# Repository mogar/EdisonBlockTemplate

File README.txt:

These are the hardware design files for a template Intel Edison Block. The Block form factor will work with the SparkFun Edison Blocks.

This template shows how you might implement your own Edison Block hardware, and includes a USB-serial converter in the schematic. The block itself is incomplete (layout still required). Add whatever functionality you want to the board.

# KiCAD libraries

See also this repo for example code:

These hardware files were created with KiCAD. You may need the KiCAD libraries available here: https://github.com/mogar/KiCAD_libs When opening these projects in KiCAD, you may need to change the path to the libraries from the above link. This can be done in preferences->libraries in both the schematic editor and the layout editor. Make sure the libraries noted there point to wherever you put the above KiCAD_libs repo.

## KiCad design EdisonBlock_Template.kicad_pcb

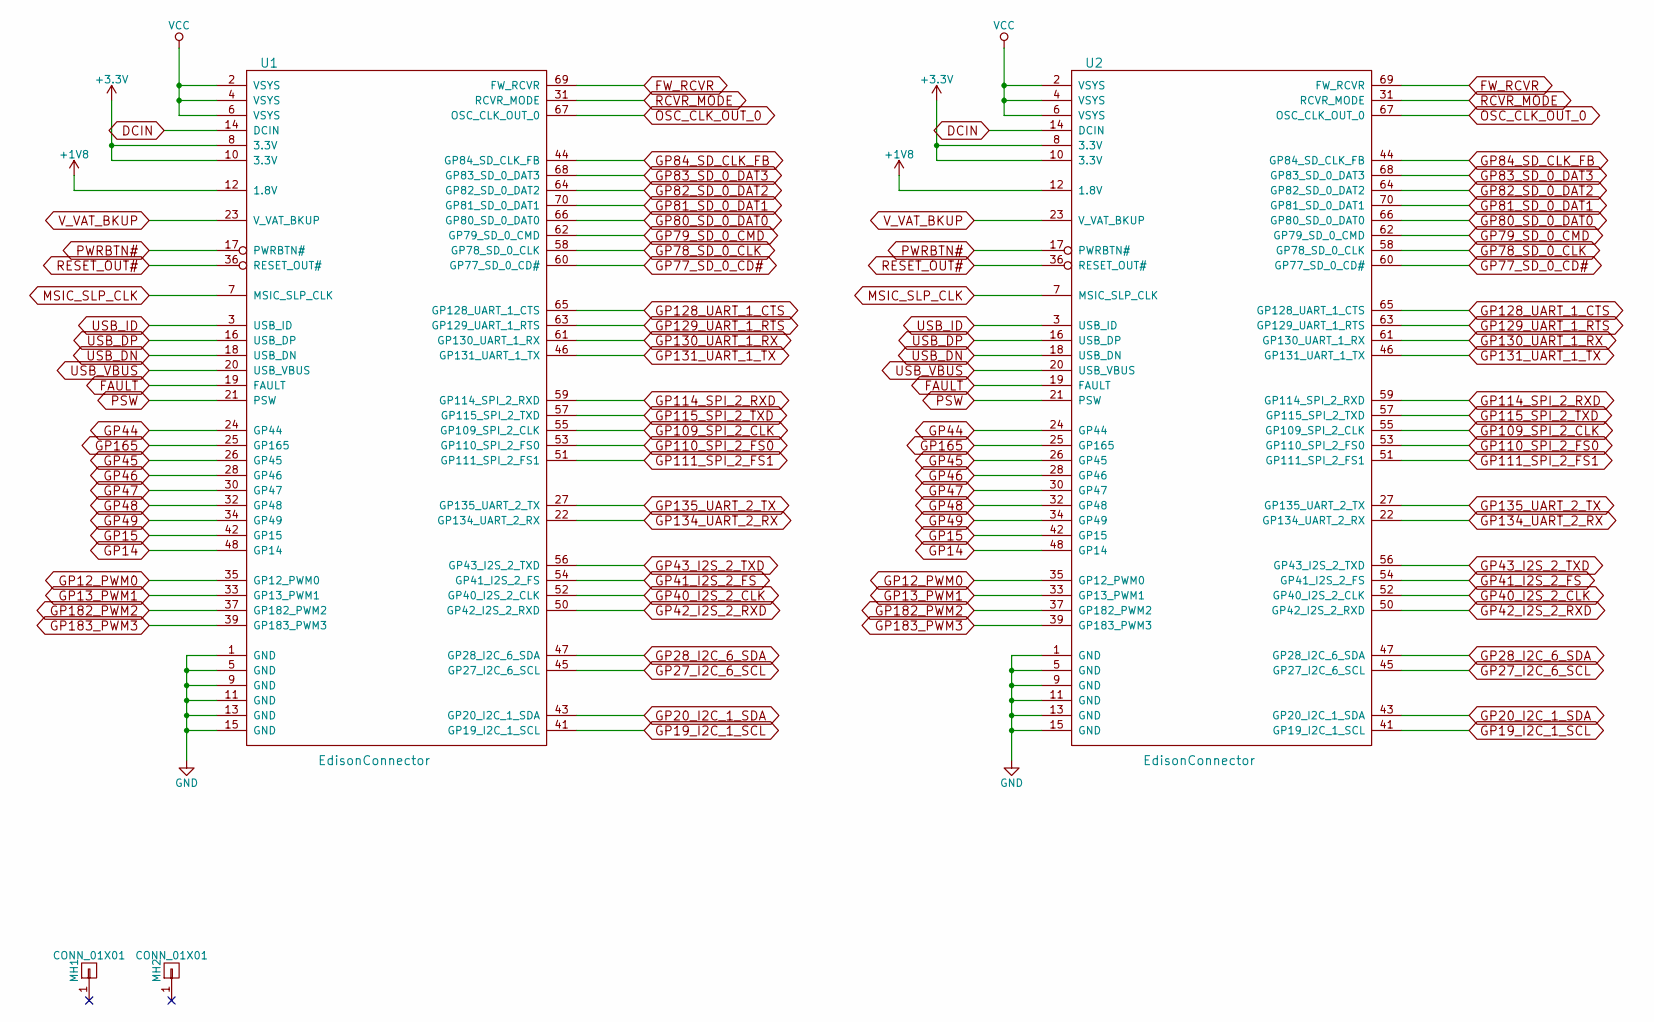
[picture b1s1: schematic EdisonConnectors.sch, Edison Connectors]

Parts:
MH1, MH2: CONN_01X01; MountingHole_2.5mm
U1: EdisonConnector; DF40HC(3.0)-70DS
U2: EdisonConnector; DF40C-70DP-0.4V(51)

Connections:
+1V8: U1.12 (1.8V), U2.12 (1.8V); also elsewhere on the board
+3V3: U1.8 (3.3V), U1.10 (3.3V), U2.8 (3.3V), U2.10 (3.3V)
DCIN: U1.14 (DCIN), U2.14 (DCIN)
FAULT: U1.19 (FAULT), U2.19 (FAULT)
FW_RCVR: U1.69 (FW_RCVR), U2.69 (FW_RCVR)
GND: U1.1 (GND), U1.5 (GND), U1.9 (GND), U1.11 (GND), U1.13 (GND), U1.15 (GND), U2.1 (GND), U2.5 (GND), U2.9 (GND), U2.11 (GND), U2.13 (GND), U2.15 (GND); also elsewhere on the board
GP12_PWM0: U1.35 (GP12_PWM0), U2.35 (GP12_PWM0)
GP13_PWM1: U1.33 (GP13_PWM1), U2.33 (GP13_PWM1)
GP14: U1.48 (GP14), U2.48 (GP14)
GP15: U1.42 (GP15), U2.42 (GP15)
GP19_I2C_1_SCL: U1.41 (GP19_I2C_1_SCL), U2.41 (GP19_I2C_1_SCL)
GP20_I2C_1_SDA: U1.43 (GP20_I2C_1_SDA), U2.43 (GP20_I2C_1_SDA)
GP27_I2C_6_SCL: U1.45 (GP27_I2C_6_SCL), U2.45 (GP27_I2C_6_SCL)
GP28_I2C_6_SDA: U1.47 (GP28_I2C_6_SDA), U2.47 (GP28_I2C_6_SDA)
GP40_I2S_2_CLK: U1.52 (GP40_I2S_2_CLK), U2.52 (GP40_I2S_2_CLK)
GP41_I2S_2_FS: U1.54 (GP41_I2S_2_FS), U2.54 (GP41_I2S_2_FS)
GP42_I2S_2_RXD: U1.50 (GP42_I2S_2_RXD), U2.50 (GP42_I2S_2_RXD)
GP43_I2S_2_TXD: U1.56 (GP43_I2S_2_TXD), U2.56 (GP43_I2S_2_TXD)
GP44: U1.24 (GP44), U2.24 (GP44)
GP45: U1.26 (GP45), U2.26 (GP45)
GP46: U1.28 (GP46), U2.28 (GP46)
GP47: U1.30 (GP47), U2.30 (GP47)
GP48: U1.32 (GP48), U2.32 (GP48)
GP49: U1.34 (GP49), U2.34 (GP49)
GP77_SD_0_CD#: U1.60 (GP77_SD_0_CD#), U2.60 (GP77_SD_0_CD#)
GP78_SD_0_CLK: U1.58 (GP78_SD_0_CLK), U2.58 (GP78_SD_0_CLK)
GP79_SD_0_CMD: U1.62 (GP79_SD_0_CMD), U2.62 (GP79_SD_0_CMD)
GP80_SD_0_DAT0: U1.66 (GP80_SD_0_DAT0), U2.66 (GP80_SD_0_DAT0)
GP81_SD_0_DAT1: U1.70 (GP81_SD_0_DAT1), U2.70 (GP81_SD_0_DAT1)
GP82_SD_0_DAT2: U1.64 (GP82_SD_0_DAT2), U2.64 (GP82_SD_0_DAT2)
GP83_SD_0_DAT3: U1.68 (GP83_SD_0_DAT3), U2.68 (GP83_SD_0_DAT3)
GP84_SD_CLK_FB: U1.44 (GP84_SD_CLK_FB), U2.44 (GP84_SD_CLK_FB)
GP109_SPI_2_CLK: U1.55 (GP109_SPI_2_CLK), U2.55 (GP109_SPI_2_CLK)
GP110_SPI_2_FS0: U1.53 (GP110_SPI_2_FS0), U2.53 (GP110_SPI_2_FS0)
GP111_SPI_2_FS1: U1.51 (GP111_SPI_2_FS1), U2.51 (GP111_SPI_2_FS1)
GP114_SPI_2_RXD: U1.59 (GP114_SPI_2_RXD), U2.59 (GP114_SPI_2_RXD)
GP115_SPI_2_TXD: U1.57 (GP115_SPI_2_TXD), U2.57 (GP115_SPI_2_TXD)
GP128_UART_1_CTS: U1.65 (GP128_UART_1_CTS), U2.65 (GP128_UART_1_CTS)
GP129_UART_1_RTS: U1.63 (GP129_UART_1_RTS), U2.63 (GP129_UART_1_RTS)
GP130_UART_1_RX: U1.61 (GP130_UART_1_RX), U2.61 (GP130_UART_1_RX)
GP131_UART_1_TX: U1.46 (GP131_UART_1_TX), U2.46 (GP131_UART_1_TX)
GP134_UART_2_RX: U1.22 (GP134_UART_2_RX), U2.22 (GP134_UART_2_RX); also elsewhere on the board
GP135_UART_2_TX: U1.27 (GP135_UART_2_TX), U2.27 (GP135_UART_2_TX); also elsewhere on the board
GP165: U1.25 (GP165), U2.25 (GP165)
GP182_PWM2: U1.37 (GP182_PWM2), U2.37 (GP182_PWM2)
GP183_PWM3: U1.39 (GP183_PWM3), U2.39 (GP183_PWM3)
MSIC_SLP_CLK: U1.7 (MSIC_SLP_CLK), U2.7 (MSIC_SLP_CLK)
OSC_CLK_OUT_0: U1.67 (OSC_CLK_OUT_0), U2.67 (OSC_CLK_OUT_0)
PSW: U1.21 (PSW), U2.21 (PSW)
PWRBTN#: U1.17 (PWRBTN#), U2.17 (PWRBTN#)
RCVR_MODE: U1.31 (RCVR_MODE), U2.31 (RCVR_MODE)
RESET_OUT#: U1.36 (RESET_OUT#), U2.36 (RESET_OUT#)
USB_DN: U1.18 (USB_DN), U2.18 (USB_DN)
USB_DP: U1.16 (USB_DP), U2.16 (USB_DP)
USB_ID: U1.3 (USB_ID), U2.3 (USB_ID)
USB_VBUS: U1.20 (USB_VBUS), U2.20 (USB_VBUS)
VCC: U1.2 (VSYS), U1.4 (VSYS), U1.6 (VSYS), U2.2 (VSYS), U2.4 (VSYS), U2.6 (VSYS); also elsewhere on the board
V_VAT_BKUP: U1.23 (V_VAT_BKUP), U2.23 (V_VAT_BKUP)

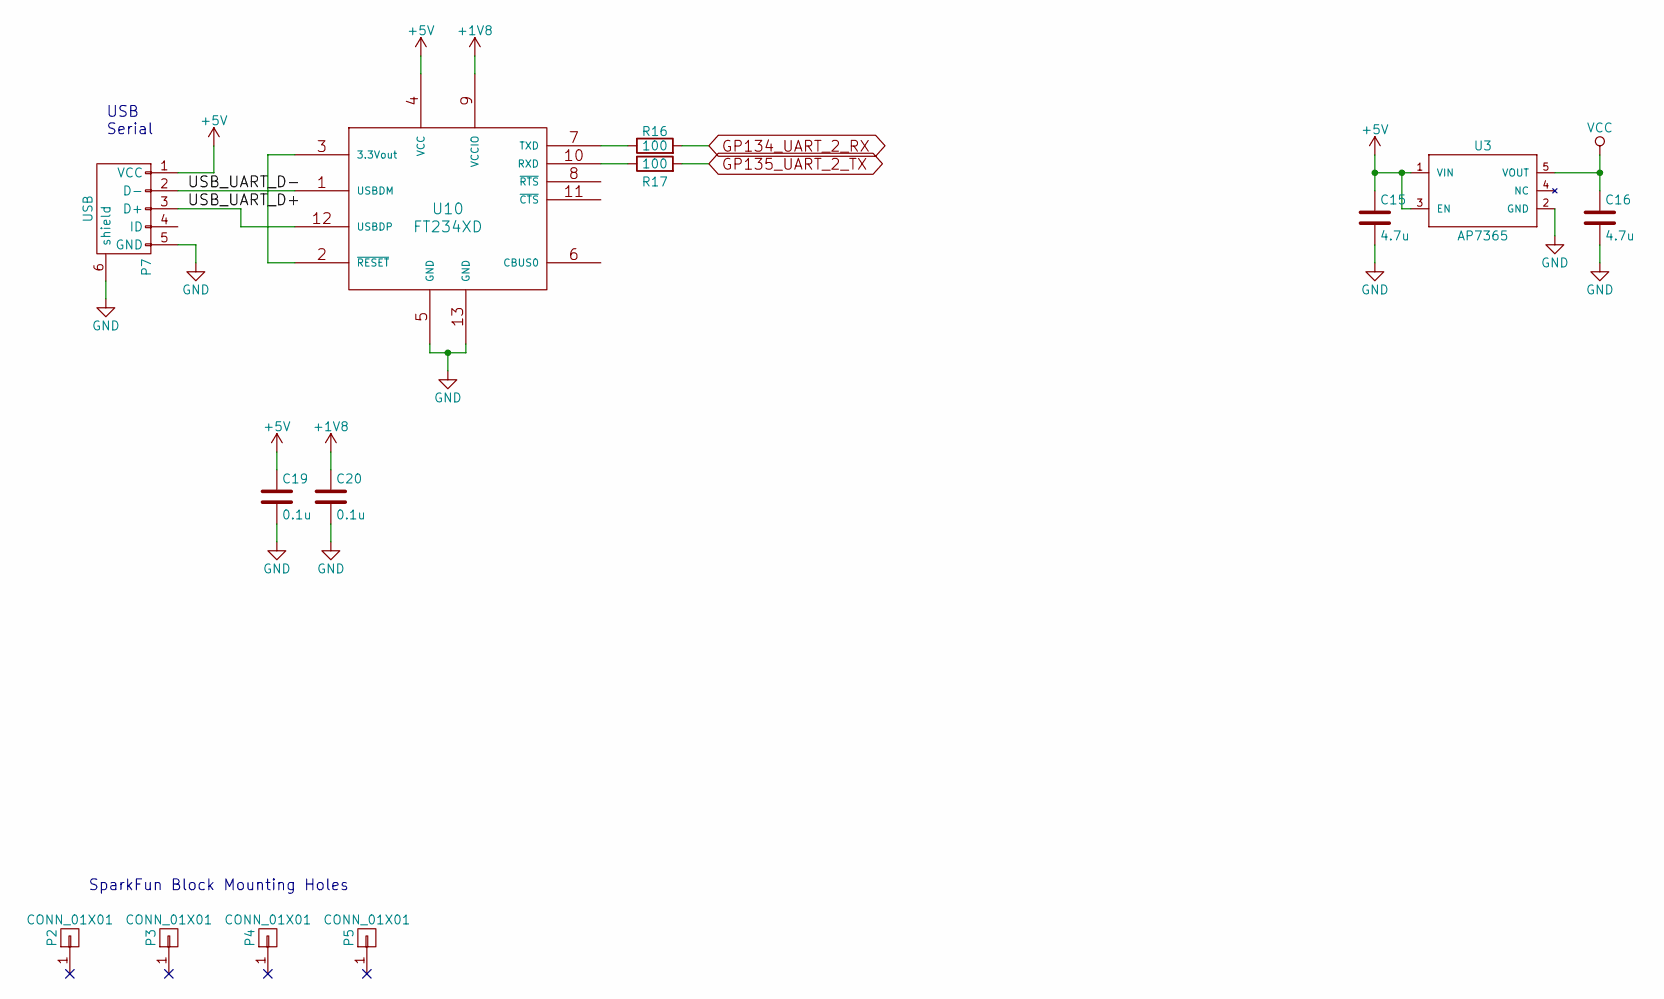
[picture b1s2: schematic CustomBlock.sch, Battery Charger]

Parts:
C15, C16: 4.7u; C_0603
C19, C20: 0.1u; C_0402
P2, P3, P4, P5: CONN_01X01; MountingHole_2.5mm
P7: USB; USB_Micro-B
R16, R17: 100; R_0603
U3: AP7365; SOT-23-5
U10: FT234XD; DFN-12-1EP_3x3mm_Pitch0.45mm

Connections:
+1V8: C20.1, U10.9 (VCCIO); also elsewhere on the board
+5V: C15.1, C19.1, P7.1 (VCC), U3.1 (VIN), U3.3 (EN), U10.4 (VCC)
/Custom Circuitry/USB_UART_D+: P7.3 (D+), U10.12 (USBDP)
/Custom Circuitry/USB_UART_D-: P7.2 (D-), U10.1 (USBDM)
GND: C15.2, C16.2, C19.2, C20.2, P7.5 (GND), P7.6 (shield), U3.2 (GND), U10.5 (GND), U10.13 (GND); also elsewhere on the board
GP134_UART_2_RX: R16.2; also elsewhere on the board
GP135_UART_2_TX: R17.2; also elsewhere on the board
unnamed: R16.1, U10.7 (TXD)
unnamed: R17.1, U10.10 (RXD)
unnamed: U10.2 (~RESET), U10.3 (3.3Vout)
VCC: C16.1, U3.5 (VOUT); also elsewhere on the board

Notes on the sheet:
SparkFun Block Mounting Holes
USB Serial

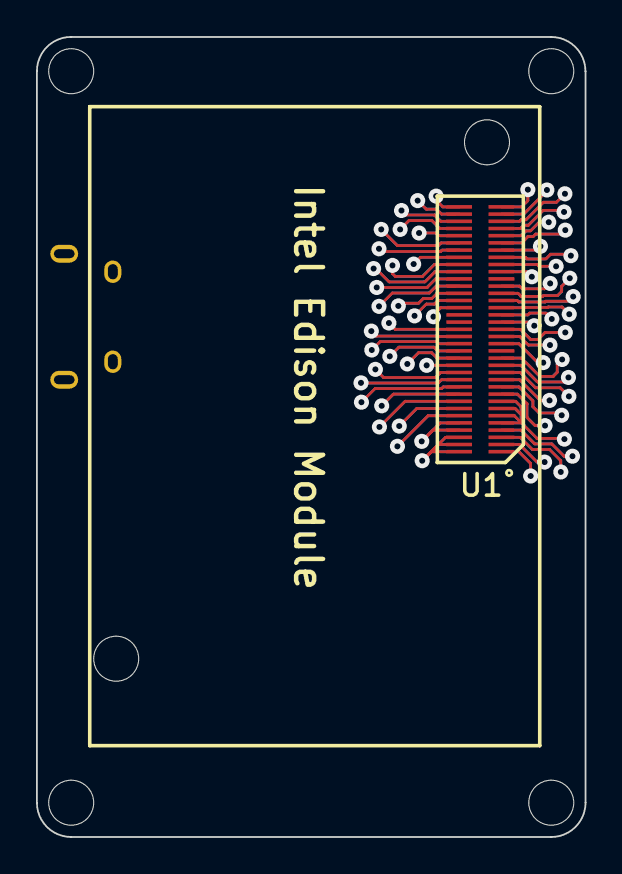
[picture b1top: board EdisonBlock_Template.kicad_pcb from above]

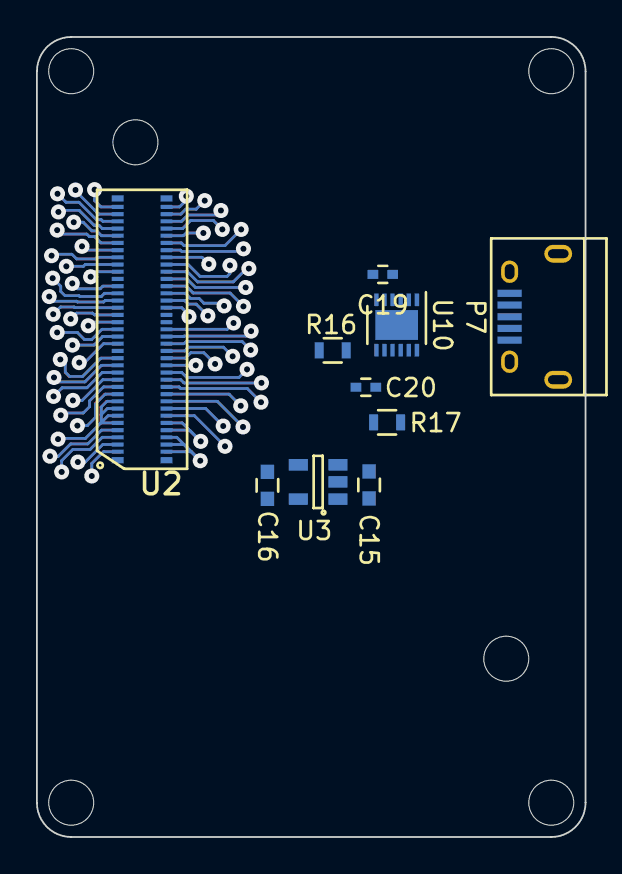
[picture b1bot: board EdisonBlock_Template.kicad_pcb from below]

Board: 2 copper layers, 30.5 x 44.5 mm, 17 parts (10 on the bottom side), 64 nets.

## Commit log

2016-09-21 basic template created
2016-09-21 rename readme
